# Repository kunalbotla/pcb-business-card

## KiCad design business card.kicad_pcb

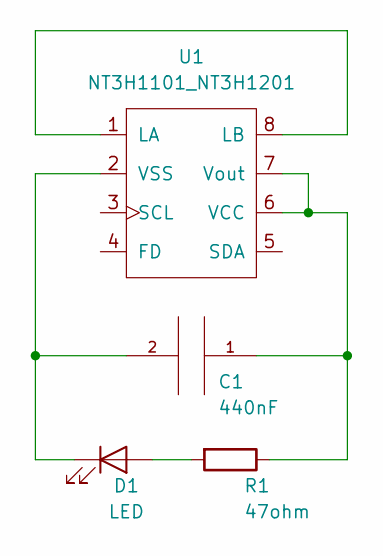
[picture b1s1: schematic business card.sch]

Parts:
C1: 440nF; C_0805_2012Metric_Pad1.15x1.40mm_HandSolder
D1: LED; LED_0805_2012Metric_Pad1.15x1.40mm_HandSolder
R1: 47ohm; R_0805_2012Metric_Pad1.15x1.40mm_HandSolder
U1: NT3H1101_NT3H1201; TSSOP-8_4.4x3mm_P0.65mm

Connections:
unnamed: C1.1, R1.1, U1.6 (VCC), U1.7 (Vout)
unnamed: C1.2, D1.1 (K), U1.2 (VSS)
unnamed: D1.2 (A), R1.2
unnamed: U1.1 (LA), U1.8 (LB)

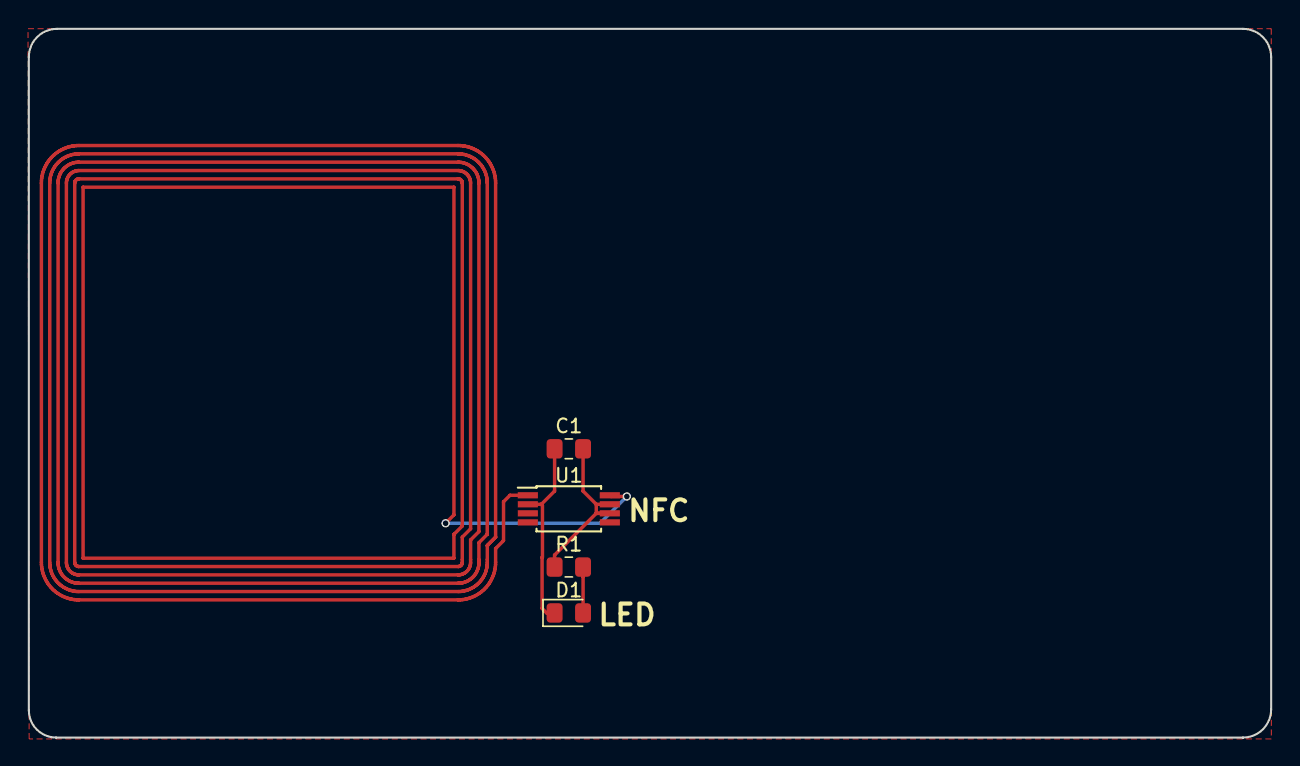
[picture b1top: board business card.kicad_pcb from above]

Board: 2 copper layers, 89.4 x 51.0 mm, 4 parts (0 on the bottom side), 4 nets.

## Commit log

2020-04-16 Changed Files
2020-04-16 Added all traces
2020-04-17 Create CNAME
2020-04-17 Card v1
2020-04-17 Card v1.1
2020-04-17 Redirect Page AND Docs Folder
2020-04-20 Create Files
2020-04-20 Fill
2020-04-20 Remove Filled Zone
2020-04-20 Gerber Files
